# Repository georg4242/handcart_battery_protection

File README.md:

# handcart_battery_protection
PCB comprising:
> uC
> batter voltage monitoring
> current monitoring
> battery relay decoupling
> fuse
> buzzer driver

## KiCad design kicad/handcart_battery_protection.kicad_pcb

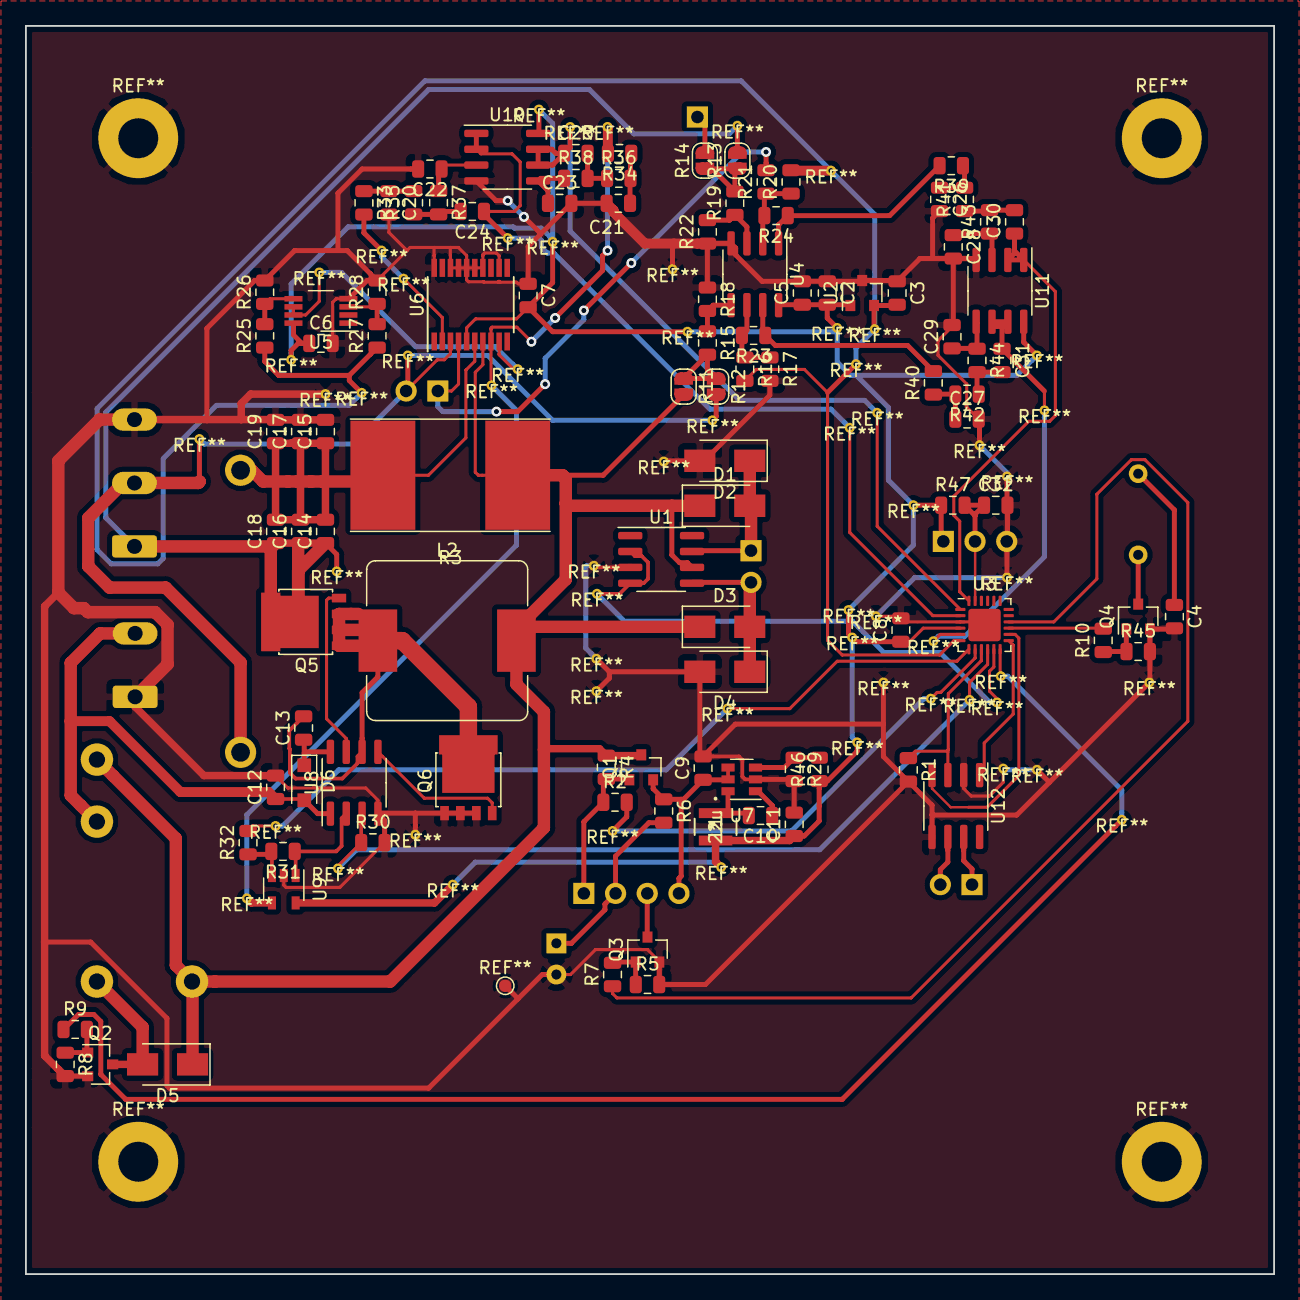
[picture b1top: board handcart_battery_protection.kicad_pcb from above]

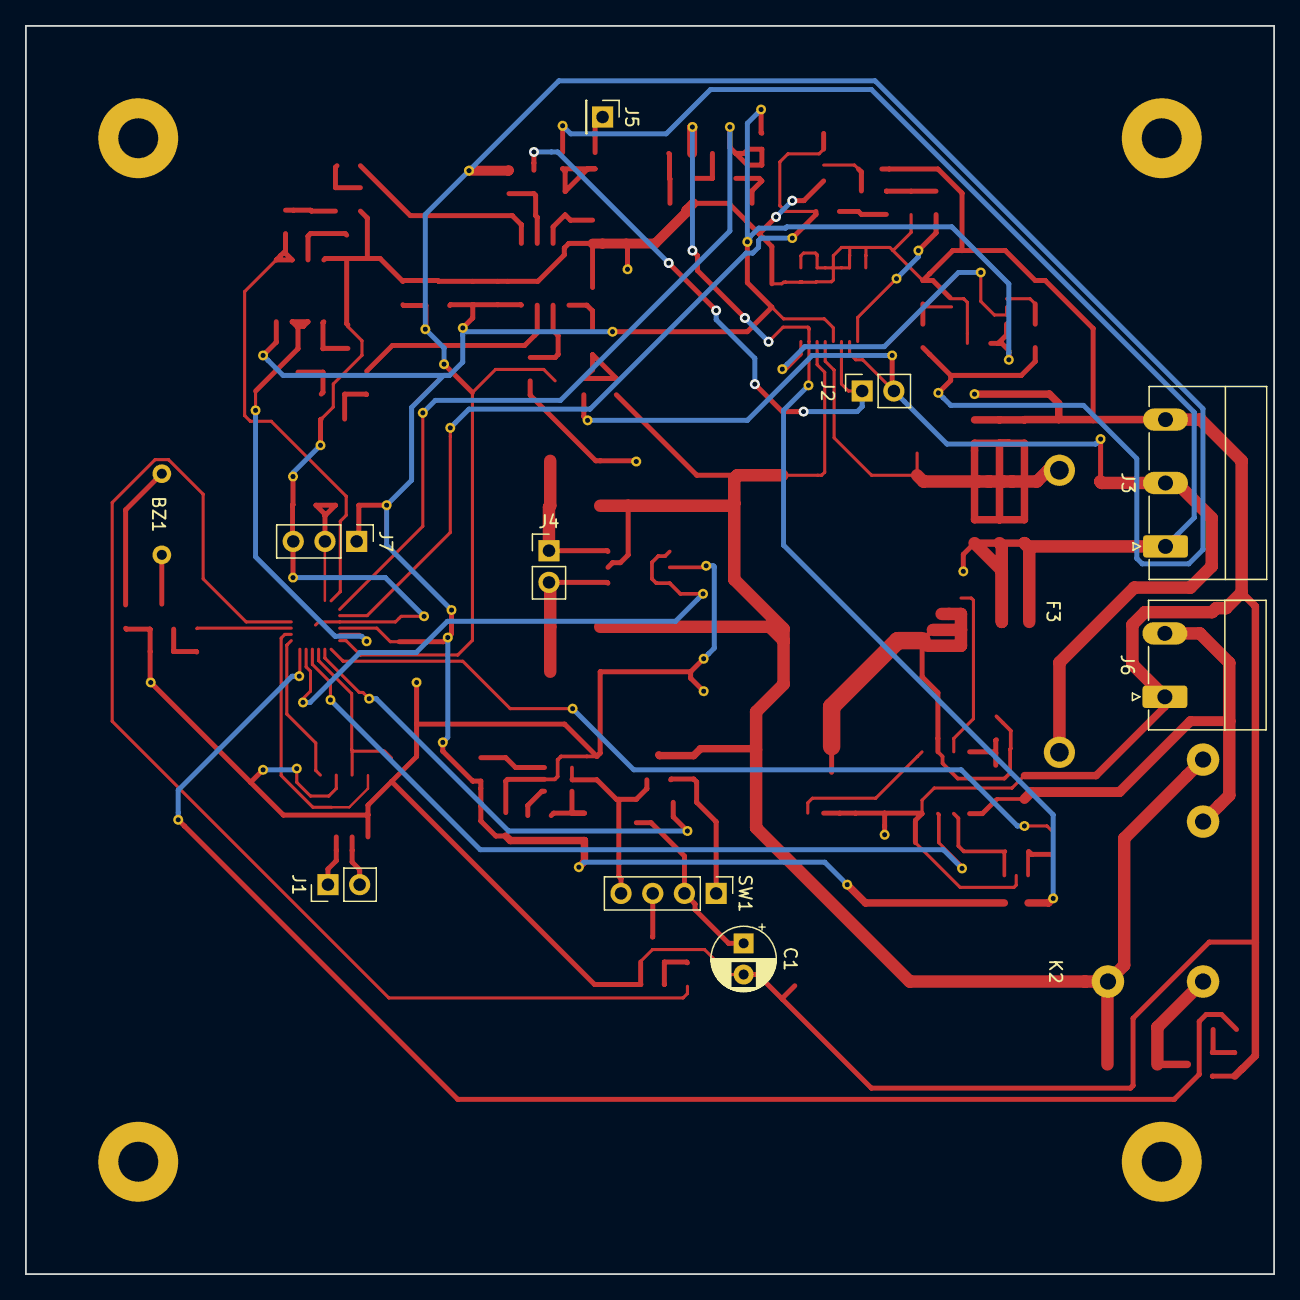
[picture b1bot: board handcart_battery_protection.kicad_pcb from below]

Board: 2 copper layers, 100.0 x 100.0 mm, 116 parts (12 on the bottom side), 74 nets.

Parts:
BZ1: Sound_Alarm_Buzzer; Sound_Buzzer
C1: 100u; CP_Radial_D5.0mm_P2.50mm
C2: 1u; C_0805_2012Metric
C3, C4, C5, C6, C7, C8, C10, C13, C32: 100n; C_0805_2012Metric
C9: 10u/50V; C_0805_2012Metric
C11, C14, C15, C16, C17, C18, C19: 22u/25V; C_0805_2012Metric
C12: 10u/25V; C_0805_2012Metric
C20, C21, C26, C27: 2.2n; C_0805_2012Metric
C22, C23, C28, C29: 150p; C_0805_2012Metric
C24, C25, C30, C31: 1n; C_0805_2012Metric
D1, D2, D3, D4, D5: BAT54-7-F; D_SMA
D6: CRH01(TE85L,Q,M); D_SOD-123F
F3: Fuse 1A, Littelfuse Inc. 39211000000; Fuse_Holder
J1: Bus; PinHeader_1x02_P2.54mm_Vertical
J2: 100A_Shunt_In; PinSocket_1x02_P2.54mm_Vertical
J3: Bat_In; PhoenixContact_MC_1,5_3-G-5.08_1x03_P5.08mm_Horizontal
J4: 100A_Relay_G9TB_Coil; PinHeader_1x02_P2.54mm_Vertical
J5: 100A_Relay_Out; PinHeader_1x01_P2.54mm_Vertical
J6: 12V_Out; PhoenixContact_MC_1,5_2-G-5.08_1x02_P5.08mm_Horizontal
J7: Program; PinHeader_1x03_P2.54mm_Vertical
K2: ALQ3F12
L1: 22u; NR3010T220M
L2: SRP1265A-470M; L_Bourns_SRP1245A
Q1: CMPDM302PH TR; SOT-23
Q2, Q3, Q4: ‎BSS816NWH6327XTSA1‎; SOT-23
Q5, Q6: PSMN013-30YLC; LFPAK
R1, R5, R6, R8, R45: 100k; R_0805_2012Metric
R2, R16, R18, R20, R22, R25, R26, R28, R29, R30: 10k; R_0805_2012Metric
R3: 1m; R_Shunt_WSLP59311
R4: 47k; R_0805_2012Metric
R7, R9, R10: 100; R_0805_2012Metric
R11, R12, R13, R14: 0; SolderJumper-2_P1.3mm_Open_RoundedPad1.0x1.5mm
R15, R19: 60k; R_0805_2012Metric
R17, R21: 40k; R_0805_2012Metric
R23, R24: 20k; R_0805_2012Metric
R27: 73.3k; R_0805_2012Metric
R31: 180k; R_0805_2012Metric
R32: 6.8k; R_0805_2012Metric
R33, R34, R39, R40: 13k; R_0805_2012Metric
R35, R36, R41, R42: 110k; R_0805_2012Metric
R37, R38, R43, R44: 39k; R_0805_2012Metric
R46: 23.7k; R_0805_2012Metric
R47: 4.7k; R_0805_2012Metric
SW1: SW_Push_LED; PinHeader_1x04_P2.54mm_Vertical
U1: TC4428; SOIC-8_3.9x4.9mm_P1.27mm
U2: REF3025; SOT-23
U3: ATtiny1617-M; QFN-24-1EP_4x4mm_P0.5mm_EP2.6x2.6mm
U4, U10, U11: LMC6482; SOIC-8_3.9x4.9mm_P1.27mm
U5: TLV9062; VSSOP-8_3.0x3.0mm_P0.65mm
U6: INA4181; TSSOP-20_4.4x6.5mm_P0.65mm
U7: TPS560430; SOT-23-6
U8: IRS2008S; SOIC-8_3.9x4.9mm_P1.27mm
U9: TLV3201; SOT-23-5
U12: ST3485; SOIC-8_3.9x4.9mm_P1.27mm

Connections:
+2V5: C3.2, R16.2, R20.2, R25.1, R27.1, U2.2, U3.6
+3V3: C2.2, C5.1, C6.1, C7.2, C8.1, C11.1, J7.1, L1.2, R46.1, R47.1, U2.1, U3.4, U4.8, U5.8, U6.5, U9.5, U10.8, U11.8
/5A_sense: C25.1, U3.1, U10.6, U10.7
/5A_sense_unfiltered: R34.2, U6.8, U9.4
/12V_Bat: C14.2, C15.1, C16.2, C17.1, C18.2, C19.1, F3.1, R3.2, U6.6
/12V_rail: D1.1, D3.1, D5.1, K2.2, K2.4, L2.2, Q1.3, R3.1, R4.1, R11.2, U1.6, U6.7
/12V_relay_ctrl: R9.1, U3.12
/12V_sense: C31.1, U3.5, U11.6, U11.7
/12V_switchable: C12.1, D6.2, J6.2, K2.3, U8.1
/24V_Bat: C14.1, C16.1, C18.1, J3.1, Q5.3, R13.2
/24V_relay_ctrl: U1.2, U1.4, U3.11
/24V_sense: C30.1, U3.24, U11.1, U11.2
/24V_switchable: J5.1, R14.2
/100A_sense: C24.1, U3.2, U10.1, U10.2
/100A_sense_H: J2.1, R21.2, U6.4
/100A_sense_L: F3.2, J2.2, J3.2, R12.2, U6.3
/BUS_A: J1.2, U12.6
/BUS_B: J1.1, U12.7
/DAC_Balancer_Vset: R32.2, U3.7
/LED: R7.1, U3.16
/TX_EN: R1.1, U3.9, U12.3
/UART_Rx: U3.13, U12.1
/UART_Tx: U3.14, U12.4
/buzzer_pwm: R10.2, U3.15
/current_monitor/0.3V: U5.1, U5.2
/current_monitor/100A_sense: R33.2, U6.2
/sound_buzzer/12V_switchable: BZ1.1, C4.1
/uC_VDD: C9.1, Q1.2, R6.1, SW1.4, U7.4, U7.5
/voltage_monitor/12V_sense: R23.1, R40.2, U4.7
/voltage_monitor/24V_sense: R24.1, R39.2, U4.1
/~BAL_Shutdown: R30.1, U3.10, U8.3
/~RESET~_UPDI: C32.1, J7.2, R47.2, U3.23
/~uC_EN: R2.2, U3.8
GND: C1.2, C2.1, C3.1, C4.2, C5.2, C6.2, C7.1, C8.2, C9.2, C11.2, C12.2, C15.2, C17.2, C19.2, C20.2, C21.2, C22.2, C23.2, C26.2, C27.2, C28.2, C29.2, C32.2, D2.2, D4.2, J3.3, J6.1, J7.3, Q2.2, Q3.2, Q4.2, Q6.1, R1.2, R5.2, R8.2, R17.2, R18.1, R22.1, R26.2, R28.2, R29.2, R30.2, R45.2, U1.3, U2.3, U3.3, U3.25, U4.4, U5.4, U6.12, U6.14, U6.15, U6.16, U6.17, U6.18, U6.20, U7.2, U8.4, U9.2, U10.4, U11.4, U12.2, U12.5
unnamed: BZ1.2, Q4.3
unnamed: C1.1, R6.2, SW1.2
unnamed: C10.1, U7.1
unnamed: C10.2, L1.1, U7.6
unnamed: C13.1, D6.1, U8.8
unnamed: C13.2, L2.1, Q5.1, Q6.3, U8.6
unnamed: C20.1, R33.1, R35.2
unnamed: C21.1, R34.1, R36.2
unnamed: C22.1, R37.1, U10.3
unnamed: C23.1, R38.1, U10.5
unnamed: C24.2, R35.1, R37.2
unnamed: C25.2, R36.1, R38.2
unnamed: C26.1, R39.1, R41.2
unnamed: C27.1, R40.1, R42.2
unnamed: C28.1, R43.1, U11.3
unnamed: C29.1, R44.1, U11.5
unnamed: C30.2, R41.1, R43.2
unnamed: C31.2, R42.1, R44.2
unnamed: D1.2, D2.1, J4.1, U1.7
unnamed: D3.2, D4.1, J4.2, U1.5
unnamed: D5.2, K2.1, Q2.3
unnamed: Q1.1, R2.1, R4.2, SW1.1
unnamed: Q2.1, R8.1, R9.2
unnamed: Q3.1, R5.1, R7.2
unnamed: Q3.3, SW1.3
unnamed: Q4.1, R10.1, R45.1
unnamed: Q5.2, U8.7
unnamed: Q6.2, U8.5
unnamed: R11.1, R12.1, R15.2
unnamed: R13.1, R14.1, R19.2
unnamed: R15.1, R18.2, U4.5
unnamed: R16.1, R17.1, R23.2, U4.6
unnamed: R19.1, R22.2, U4.3
unnamed: R20.1, R21.1, R24.2, U4.2
unnamed: R25.2, R26.1, U5.5
unnamed: R27.2, R28.1, U5.3
unnamed: R29.1, R46.2, U7.3
unnamed: R31.1, U8.2, U9.1
unnamed: R31.2, R32.1, U9.3
unnamed: U5.6, U5.7, U6.9

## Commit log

2019-05-12 Files added
2019-05-12 Added license file.
2019-05-12 Added pdf.
2019-05-26 Stand Do 16.05.19.
2019-05-27 Balancer added.
2019-05-30 Balancer added. Schematic should be finished.
2019-05-30 Added sch files.
2019-05-30 Terminals for Bat, 100A-relais, 100A-shunt and etc.
2019-05-30 Small changes. Footprints associated.
2019-05-31 Layout done. Traces only on one PCB side. Wire bridges necessary.
2019-05-31 Added Bottom-layer-traces. Added ground plane. PCB outline shrinked to 100x100.

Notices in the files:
parts and their libraries:
Copyright 2016 Accelerated Designs. All rights reserved.
